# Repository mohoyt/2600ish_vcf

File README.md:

# 2600ish_vcf

This is a fully through hole component Eurorack voltage controlled low pass filter based on the one in the ARP 2600. There were different filters in the ARP 2600 at different times, this is the 4072 variety and is not a diode ladder filter like the early one. 

Inspiration and the starting point for schematics for this filter taken from [Eddy Bergman](https://www.eddybergman.com/2020/03/synthesizer-build-part-21-arp2600.html) and [Yusynth](http://yusynth.net/Modular/EN/ARPVCF/index.html)

This module is 10hp (~50mm) wide and runs on a standard dual rail 12v eurorack supply.

See a longer write up of this project on my website: [https://mohoyt.com/blog/2024/2600ish-vcf](https://mohoyt.com/blog/2024/2600ish-vcf)

Special thanks to [PCBWay](https://pcbway.com) for sponsoring this build.

## Samples

See [samples](samples) folder or examples on Soundcloud:
- [Triangle wave](https://soundcloud.com/moses-hoyt/2600ish-vcf-triangle-wave)
- [Square wave](https://soundcloud.com/moses-hoyt/2600ish-vcf-square-wave)
- [Sawtooth wave](https://soundcloud.com/moses-hoyt/2600ish-vcf-sawtooth-wave)

## Gerbers

See the most recent gerbers on the releases tab. The gerbers included are configured for PCBWay. There are two sets, one for the panel and one for the PCB. 

## Bill of Materials

See the iBOM in the [BOM](bom) folder. You will need matched 2N3906 transistors and ideally polystyrene caps for the four filter poles.

## Calibration and tuning 

Taken from [Yusynth](http://yusynth.net/Modular/index_en.html)

### V/Octave tracking:
- Turn the frequency knob to 0, turn all the control knobs to 0 (fully counter clockwise)
- Apply 0V to the V/Oct input
- Measure the voltage at the basis of Q3 (node between R46, R30 to R34), adjust T1 (low freq trimmer) in order to obtain 0V at this very node.
- Apply 1V to the V/Oct input
- Adjust T2 (v/octave trimmer) in order to measure 18.7mV at the previous node.
- Apply 0V to the V/Oct input
- Adjust T1 (low freq trimmer) in order to measure -187mV at this very node.
- After the Frequency range stting (see below) you may set the filter to oscilltion mode and slightly adjust T2 in order to achieve a good V/Octave tracking.

### Frequency range setting :
- Apply a 40Hz squarewave to one of the audio input, connect the output to an amplifier.
- Set the FREQUENCY potentiometer to 0 (fully counter clockwise)
- Adjust T1 (low freq trimmer) until no signal can be heard at the output, that's it!

## Notes and known issues
- v0.1 had an issue with an extra connection around R9, but fixable on the board by rerouting R9, cutting traces and adding a bodge wire. This is fixed in v0.2
- For the panel ensure that the silkscreen is *not* subtracted from the soldermask otherwise parts of the lines and words will be difficult to read

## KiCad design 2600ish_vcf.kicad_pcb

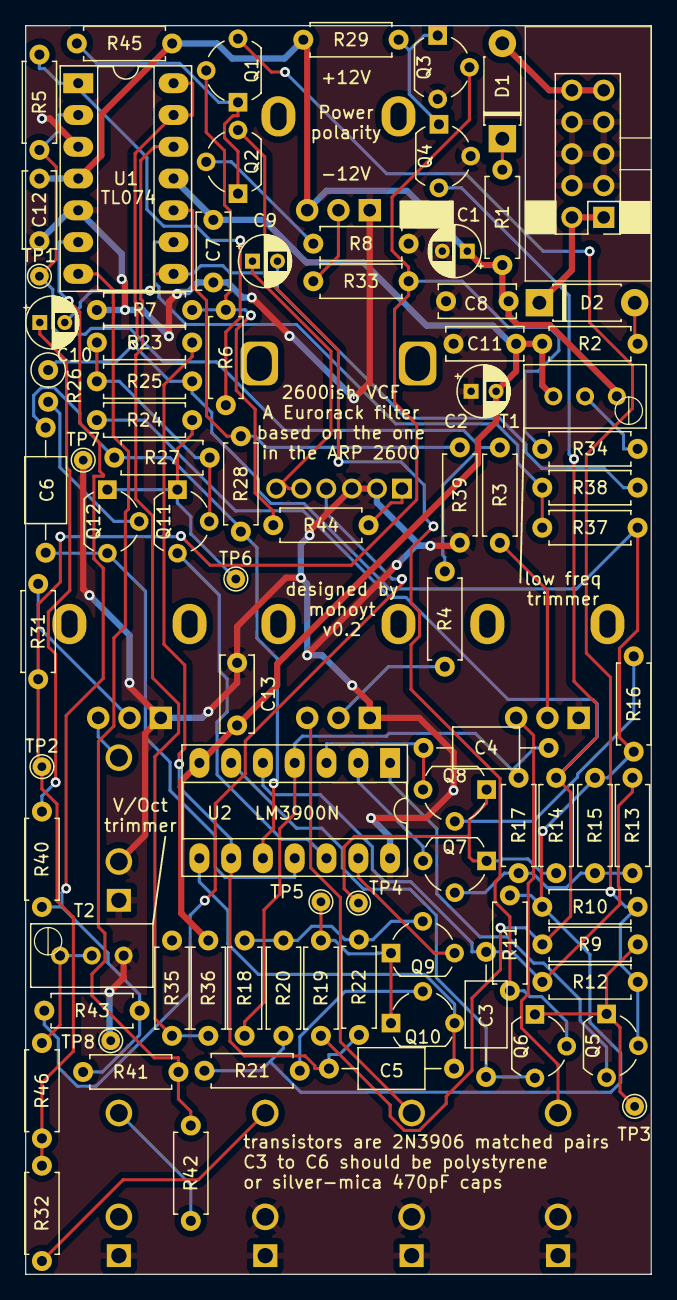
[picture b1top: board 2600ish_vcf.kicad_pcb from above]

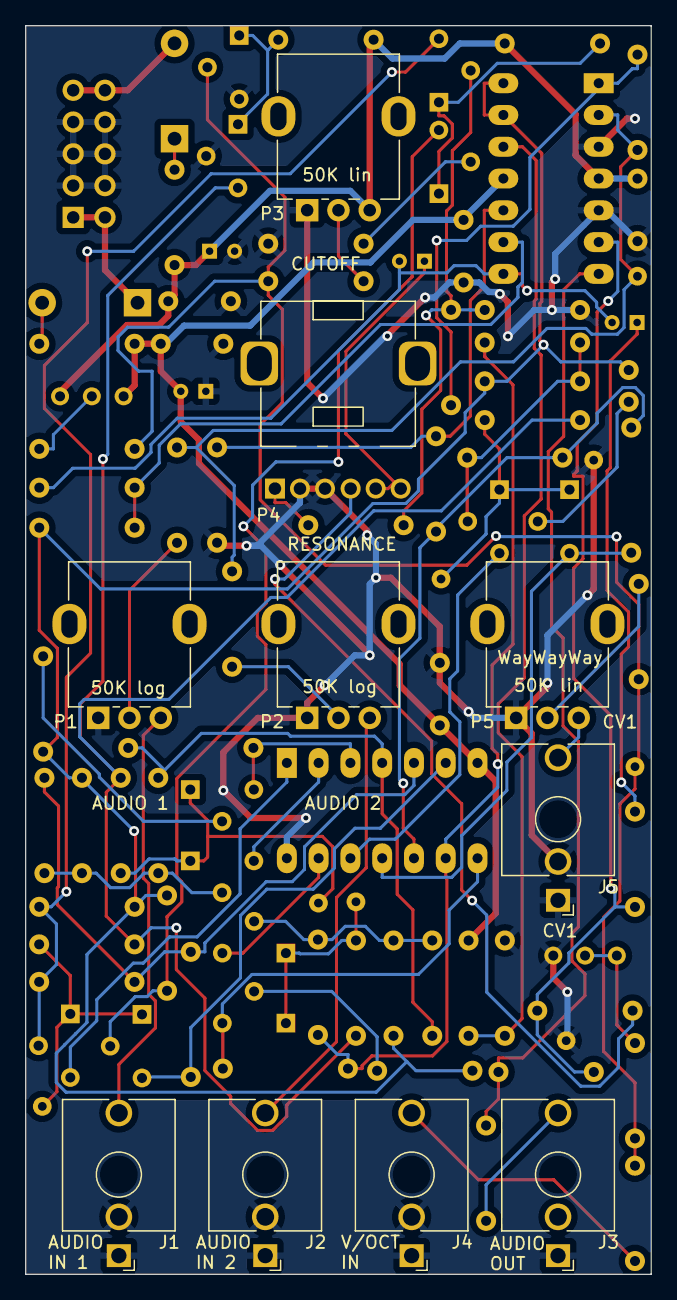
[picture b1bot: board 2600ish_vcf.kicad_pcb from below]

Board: 2 copper layers, 50.0 x 99.8 mm, 95 parts (10 on the bottom side), 61 nets.

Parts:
C1, C2: 47uF; CP_Radial_D4.0mm_P2.00mm
C3, C4, C5, C6: 470pF; C_Axial_L5.1mm_D3.1mm_P10.00mm_Horizontal
C7, C8, C11, C12, C13: 0.1uF; C_Disc_D6.0mm_W2.5mm_P5.00mm
C9, C10: 22uF; CP_Radial_D4.0mm_P2.00mm
CONN1: Conn_01x10; PinHeader_2x05_P2.54mm_Vertical_Shroud
D1, D2: 1N5819; D_DO-41_SOD81_P7.62mm_Horizontal
J1: AUDIO IN 1; Jack_3.5mm_QingPu_WQP-PJ398SM_Vertical_CircularHoles
J2: AUDIO IN 2; Jack_3.5mm_QingPu_WQP-PJ398SM_Vertical_CircularHoles
J3: OUT; Jack_3.5mm_QingPu_WQP-PJ398SM_Vertical_CircularHoles
J4: V/OCT IN; Jack_3.5mm_QingPu_WQP-PJ398SM_Vertical_CircularHoles
J5: CV 1; Jack_3.5mm_QingPu_WQP-PJ398SM_Vertical_CircularHoles
P1, P2: 50K log; Potentiometer_Alpha_RD901F-40-00D_Single_Vertical
P3, P5: 50K lin; Potentiometer_Alpha_RD901F-40-00D_Single_Vertical
P4: 100k; Potentiometer_Double_Vertical_Befaco
Q1, Q2, Q3, Q4, Q5, Q6, Q7, Q8, Q9, Q10, Q11, Q12: 2N3906; TO-92_Wide
R1, R2: 10; R_Axial_DIN0207_L6.3mm_D2.5mm_P7.62mm_Horizontal
R3, R4, R5, R6, R31, R32, R34, R39, R41: 100k; R_Axial_DIN0207_L6.3mm_D2.5mm_P7.62mm_Horizontal
R7, R9, R14, R19, R24, R42, R46: 1k; R_Axial_DIN0207_L6.3mm_D2.5mm_P7.62mm_Horizontal
R8, R10, R11, R15, R16, R20, R21, R25: 220R; R_Axial_DIN0207_L6.3mm_D2.5mm_P7.62mm_Horizontal
R12, R13, R17, R18, R22, R23, R27, R28, R29, R36, R37, R38: 10k; R_Axial_DIN0207_L6.3mm_D2.5mm_P7.62mm_Horizontal
R26: 220R; R_Axial_DIN0207_L6.3mm_D2.5mm_P2.54mm_Vertical
R33: 150k; R_Axial_DIN0207_L6.3mm_D2.5mm_P7.62mm_Horizontal
R35: 10k or 18k; R_Axial_DIN0207_L6.3mm_D2.5mm_P7.62mm_Horizontal
R40: 56k; R_Axial_DIN0207_L6.3mm_D2.5mm_P7.62mm_Horizontal
R43: 22k; R_Axial_DIN0207_L6.3mm_D2.5mm_P7.62mm_Horizontal
R44: 15k; R_Axial_DIN0207_L6.3mm_D2.5mm_P7.62mm_Horizontal
R45: 33k; R_Axial_DIN0207_L6.3mm_D2.5mm_P7.62mm_Horizontal
T1: 50K trimmer; Potentiometer_Bourns_3296W_Vertical
T2: 2k trimmer; Potentiometer_Bourns_3296W_Vertical
TP1, TP2, TP3, TP4, TP5, TP6, TP7, TP8: TestPoint; TestPoint_THTPad_D1.5mm_Drill0.7mm
U1: TL074; DIP-14_W7.62mm_Socket_LongPads
U2: LM3900N; DIP-14_W7.62mm_Socket_LongPads

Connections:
+12V: C1.1, C8.1, C12.1, P3.3, R1.2, R29.2, R45.2, T1.1, U1.4 (V+)
-12V: C2.2, C7.2, C11.2, C13.2, R2.2, R36.2, T1.3, U1.11 (V-), U2.7 (GND)
AUDIO OUT: R41.2, R42.2, U1.7
AUDIOS IN: R3.2, R4.2, R5.1, TP1.1, U1.2 (-)
CUTOFF: Q3.2 (B), R31.2, R32.2, R33.2, R34.1, R46.2, TP2.1
GND: C1.2, C2.1, C7.1, C8.2, C11.1, C12.2, C13.1, CONN1.3, CONN1.4, CONN1.5, CONN1.6, CONN1.7, CONN1.8, J1.S, J1.TN, J2.S, J2.TN, J3.S, J4.S, J4.TN, J5.S, J5.TN, P1.1, P2.1, P3.1, P4.1, P4.4, P5.1, Q3.3 (C), Q4.2 (B), R7.1, R8.1, R35.1, R39.1, T2.3, TP7.1, TP8.1, U1.3 (+), U1.5 (+), U2.14 (VCC)
unnamed: C3.2, R12.1, R13.2, U2.5
unnamed: C4.2, R17.1, R18.2, U2.4
unnamed: C5.2, R22.1, R23.2, U2.9
unnamed: C6.2, R27.1, R28.1, U2.10
unnamed: C10.1, R40.1
unnamed: C9.2, C10.2, R38.2, U1.8
unnamed: CONN1.1, CONN1.2, D2.1 (K)
unnamed: CONN1.9, CONN1.10, D1.2 (A)
unnamed: D1.1 (K), R1.1
unnamed: D2.2 (A), R2.1
unnamed: J1.T, P1.3
unnamed: J2.T, P2.3
unnamed: J3.T, R42.1
unnamed: J4.T, R32.1
unnamed: J5.T, P5.3
unnamed: P1.2, R3.1
unnamed: P2.2, R4.1
unnamed: P3.2, R33.1
unnamed: P4.2, R44.1
unnamed: P5.2, R31.1
unnamed: Q1.3 (C), Q5.2 (B), R10.2, R12.2
unnamed: Q1.1 (E), Q2.1 (E), R45.1
unnamed: Q2.2 (B), R8.2
unnamed: Q2.3 (C), Q6.2 (B), R11.2
unnamed: Q3.1 (E), Q4.1 (E), R29.1
unnamed: Q4.3 (C), R9.1, R14.1, R19.1, R24.1
unnamed: Q5.3 (C), U2.1 (+)
unnamed: Q5.1 (E), Q6.1 (E), R9.2, TP3.1
unnamed: C3.1, Q6.3 (C), U2.6 (-)
unnamed: Q7.2 (B), R13.1, R15.2, R17.2
unnamed: Q7.3 (C), U2.2 (+)
unnamed: Q7.1 (E), Q8.1 (E), R14.2, TP4.1
unnamed: Q8.2 (B), R16.2
unnamed: C4.1, Q8.3 (C), U2.3 (-)
unnamed: Q9.2 (B), R18.1, R20.2, R22.2
unnamed: Q9.3 (C), U2.13 (+)
unnamed: Q10.2 (B), R21.2
unnamed: C5.1, Q10.3 (C), U2.8 (-)
unnamed: Q9.1 (E), Q10.1 (E), R19.2, TP5.1
unnamed: Q11.2 (B), R23.1, R25.2, R27.2
unnamed: Q11.3 (C), U2.12 (+)
unnamed: Q11.1 (E), Q12.1 (E), R24.2, TP6.1
unnamed: Q12.2 (B), R26.2
unnamed: C6.1, Q12.3 (C), U2.11 (-)
unnamed: R5.2, R6.1, U1.1
unnamed: R34.2, T1.2
unnamed: R46.1, T2.1, T2.2
unnamed: R40.2, R41.1, R43.1, U1.6 (-)
unnamed: R28.2, R39.2, U1.10 (+)
unnamed: R37.2, R38.1, U1.9 (-)
unnamed: R35.2, R36.1, U1.12 (+)
unnamed: R10.1, R11.1, R15.1, R16.1, R20.1, R21.1, R25.1, R26.1, R37.1, U1.13 (-), U1.14
RESONANCE 1: Q1.2 (B), R6.2, R7.2, R44.2
RESONANCE 2: P4.5, R43.2
RESONANCE 3: C9.1, P4.3, P4.6

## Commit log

2024-02-07 Schematic done mostly
2024-03-19 PCB layout started
2024-03-21 component placement done
2024-03-21 Some adjustments made for gain and footprint size
2024-03-26 Clearer schematic
2024-03-26 Schematic for split board done, updating PCB now
2024-03-26 Main PCB pretty much done, panel work started
2024-03-31 New panel design with topography
2024-04-02 BOM added
2024-04-11 Schematic issue and related routing fixed and v0.2 created. New gerbers generated
2024-04-11 Readme made clearer
2024-04-15 Readme updated and photos added
2024-04-15 Readme updated and license added
2024-04-15 Readme update
2024-04-16 Samples added
